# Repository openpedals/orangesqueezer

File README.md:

## Orange Squeezer

An Orange Squeezer clone made with KiCad.

## Todo

- [ ] Copy values from the original schematic
- [ ] Do floorplanning
- [ ] Do routing
- [ ] Get a template for the io jacks
- [ ] Get a template for the 3PDT switch PCB

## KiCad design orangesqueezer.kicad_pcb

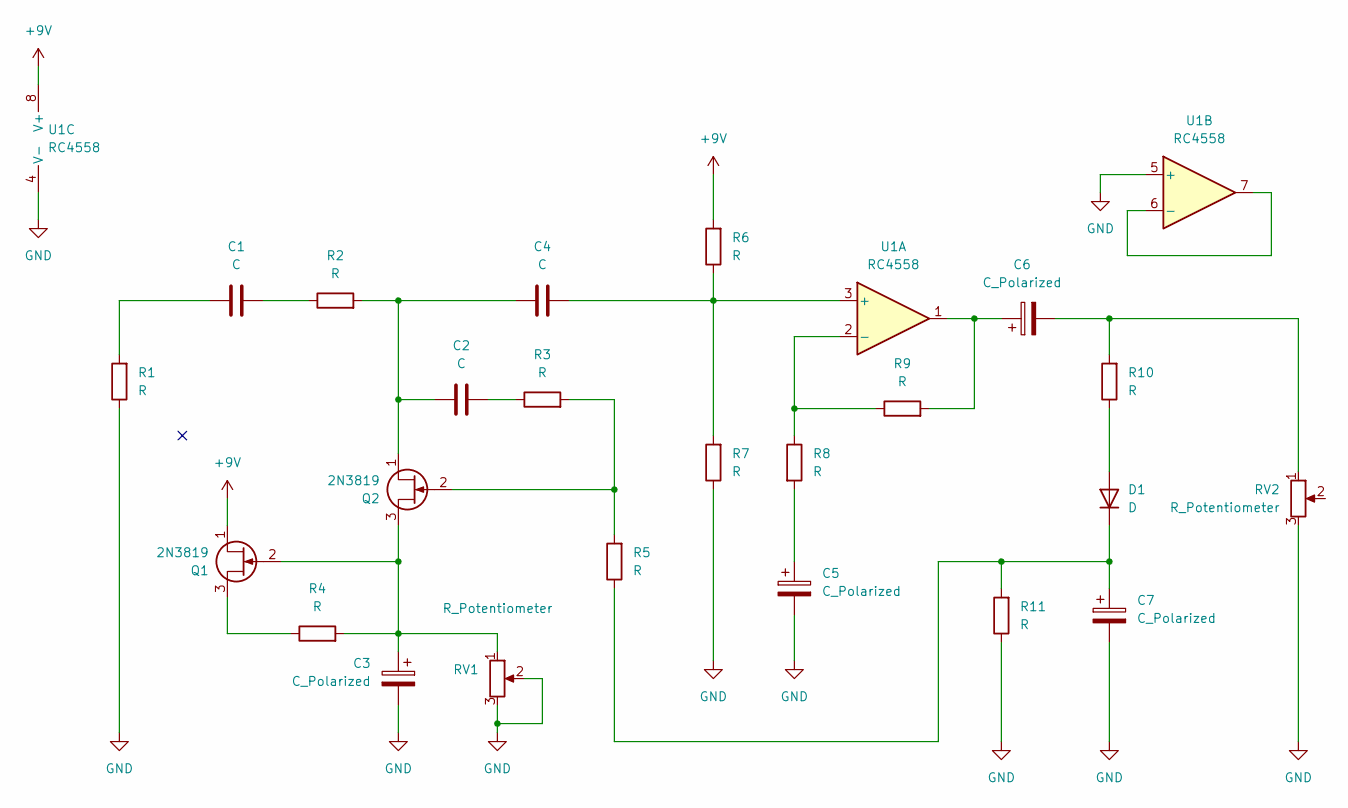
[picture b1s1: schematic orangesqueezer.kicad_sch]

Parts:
C1, C2, C4: C; C_Disc_D7.5mm_W2.5mm_P5.00mm
C3, C5, C6, C7: C_Polarized; CP_Radial_D5.0mm_P2.50mm
D1: D; R_Axial_DIN0204_L3.6mm_D1.6mm_P5.08mm_Horizontal
Q1, Q2: 2N3819; TO-92
R1, R2, R3, R4, R5, R6, R7, R8, R9, R10, R11: R; R_Axial_DIN0204_L3.6mm_D1.6mm_P5.08mm_Horizontal
RV1, RV2: R_Potentiometer; Potentiometer_Alps_RK163_Single_Horizontal
U1: RC4558; DIP-8_W7.62mm_Socket

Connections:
+9V: Q1.1 (D), R6.2, U1.8 (V+)
GND: C3.2, C5.2, C7.2, R1.1, R7.1, R11.1, RV1.2, RV1.3, RV2.3, U1.4 (V-), U1.5 (+)
unnamed: C1.1, R1.2
unnamed: C1.2, R2.1
unnamed: C2.2, R3.1
unnamed: C5.1, R8.2
unnamed: C6.1, R9.2, U1.1
unnamed: C6.2, R10.2, RV2.1
unnamed: D1.2 (A), R10.1
unnamed: C7.1, D1.1 (K), R5.1, R11.2
unnamed: C3.1, Q1.2 (G), Q2.3 (S), R4.2, RV1.1
unnamed: Q1.3 (S), R4.1
unnamed: C2.1, C4.1, Q2.1 (D), R2.2
unnamed: Q2.2 (G), R3.2, R5.2
unnamed: C4.2, R6.1, R7.2, U1.3 (+)
unnamed: R8.1, R9.1, U1.2 (-)
unnamed: U1.6 (-), U1.7

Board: 2 copper layers, 24 parts (0 on the bottom side), 17 nets, no tracks yet.

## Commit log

2024-09-22 Initial commit. Checkin all the draft files
